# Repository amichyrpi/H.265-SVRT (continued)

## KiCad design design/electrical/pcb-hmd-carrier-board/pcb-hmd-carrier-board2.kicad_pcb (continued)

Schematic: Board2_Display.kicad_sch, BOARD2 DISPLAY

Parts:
C260, C265: 2.2uF; C_0603_1608Metric
C261, C262, C266, C267: 1uF 10V; C_0603_1608Metric
C270, C272, C273: 4.7uF 10V; C_0603_1608Metric
C271: 2.2uF 10V; C_0603_1608Metric
C274: 1uF; C_0603_1608Metric
C280: 68n COMP; C_0402_1005Metric
C281: 10uF 10V; C_0402_1005Metric
C282, C283: 10uF 16V; C_0402_1005Metric
C290, C291: 100n; C_0402_1005Metric
D201: DFLS160-7; D_SOD-123
J201: J_DISPLAY_LEFT 245863050104829+; Kyocera_245863050104829_50P_P0.35
J202: J_DISPLAY_RIGHT 245863050104829+; Kyocera_245863050104829_50P_P0.35
L203, L204, L205, L206: 2.2uH; L_Abracon_ASPI-4030S
L207: 4.7uH 1.6A DFE252010; L_APV_ANR252010
L208: 10uH >=2.5A WLED; L_Abracon_ASPI-4030S
R260, R265: 100k RESET pulldown; R_0402_1005Metric
R261, R266: 0R DNP to BL_PWM; R_0402_1005Metric; not fitted
R280: 37.4k 1% ISET=33.2mA; R_0402_1005Metric
R281: 49.9k 1% 1.25MHz; R_0402_1005Metric
R282: 147k 1% OVP; R_0402_1005Metric
R283: 20k 1% OVP; R_0402_1005Metric
R284: 3k COMP; R_0402_1005Metric
R290, R291, R292, R293: 2.2k I2C; R_0402_1005Metric
R294, R295: 10k; R_0402_1005Metric
TP201: DISPLAY_5V; TestPoint_Pad_D1.0mm
TP202: DISPLAY_3V3; TestPoint_Pad_D1.0mm
TP203: DISPLAY_1V8; TestPoint_Pad_D1.0mm
TP204: DISPLAY_1V2; TestPoint_Pad_D1.0mm
TP205: DISPLAY_1V15; TestPoint_Pad_D1.0mm
TP206: LCD_VSP +5V5; TestPoint_Pad_D1.0mm
TP207: LCD_VSN -5V5; TestPoint_Pad_D1.0mm
TP208: BL_EN; TestPoint_Pad_D1.0mm
TP209: BL_PWM GPIO12; TestPoint_Pad_D1.0mm
TP210: I2C_SDA_1V8; TestPoint_Pad_D1.0mm
TP211: I2C_SCL_1V8; TestPoint_Pad_D1.0mm
TP260: L S1_TEST NC; TestPoint_Pad_D1.0mm
TP261: L TE; TestPoint_Pad_D1.0mm
TP262: L LEDPWM; TestPoint_Pad_D1.0mm
TP265: R S1_TEST NC; TestPoint_Pad_D1.0mm
TP266: R TE; TestPoint_Pad_D1.0mm
TP267: R LEDPWM; TestPoint_Pad_D1.0mm
U201, U202: TC358870XBG(NOK) C3008712; Toshiba_P-VFBGA80_7x7mm_P0.65
U203, U204, U205, U206: TLV62569DBVR; SOT-23-5
U207: TPS65132B5YFFR; TI_DSBGA15_YFF_2.108x1.514mm_P0.4
U208: MP3387AGRT-P; TQFN-24-1EP_4x4mm_P0.5mm_EP2.6x2.6mm
U209: PCA9306DCTR C123752; TSSOP-8_3x3mm_P0.65mm
Y201, Y202: SIT8008ACE73-18E-48.000000E; Oscillator_SMD_SiT_PQFN-4Pin_2.0x1.6mm

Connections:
+3V3: R290.2 (+3V3), R291.2 (+3V3), U209.2 (+3V3); also elsewhere on the board
+5V_SYS: C270.1 (+5V_SYS), C281.1 (+5V_SYS), L207.1 (+5V_SYS), L208.1 (+5V_SYS), TP201.1, U203.1 (+5V_SYS), U203.4 (+5V_SYS), U204.1 (+5V_SYS), U204.4 (+5V_SYS), U205.1 (+5V_SYS), U205.4 (+5V_SYS), U206.1 (+5V_SYS), U206.4 (+5V_SYS), U207.C1 (+5V_SYS), U208.23 (+5V_SYS), U208.24 (+5V_SYS); also elsewhere on the board
BIAS_FLY1: C271.1 (BIAS_FLY1), U207.C3 (BIAS_FLY1)
BIAS_FLY2: C271.2 (BIAS_FLY2), U207.A3 (BIAS_FLY2)
BIAS_REG: C274.1 (BIAS_REG), U207.D3 (BIAS_REG), U207.E2 (BIAS_REG)
BIAS_SW: L207.2 (BIAS_SW), U207.D1 (BIAS_SW)
BL_EN: TP208.1, U208.1 (BL_EN); also elsewhere on the board
BL_PWM: R261.2 (BL_PWM), R266.2 (BL_PWM), TP209.1, U208.6 (BL_PWM); also elsewhere on the board
DISPLAY_1V2: L205.2 (DISPLAY_1V2), TP204.1; also elsewhere on the board
DISPLAY_1V8: C260.1 (DISPLAY_1V8), C265.1 (DISPLAY_1V8), C290.1 (DISPLAY_1V8), C291.1 (DISPLAY_1V8), J201.2 (DISPLAY_1V8), J201.4 (DISPLAY_1V8), J202.2 (DISPLAY_1V8), J202.4 (DISPLAY_1V8), L204.2 (DISPLAY_1V8), R292.2 (DISPLAY_1V8), R293.2 (DISPLAY_1V8), R294.2 (DISPLAY_1V8), R295.2 (DISPLAY_1V8), TP203.1, U209.3 (DISPLAY_1V8), U209.4 (DISPLAY_1V8), Y201.1 (DISPLAY_1V8), Y201.4 (DISPLAY_1V8), Y202.1 (DISPLAY_1V8), Y202.4 (DISPLAY_1V8); also elsewhere on the board
DISPLAY_1V15: L206.2 (DISPLAY_1V15), TP205.1; also elsewhere on the board
DISPLAY_3V3: L203.2 (DISPLAY_3V3), TP202.1; also elsewhere on the board
DISPLAY_GPIO_INT_N: R295.1 (DISPLAY_GPIO_INT_N); also elsewhere on the board
DISPLAY_GPIO_RESETN: R294.1 (DISPLAY_GPIO_RESETN); also elsewhere on the board
DISPLAY_I2C_SCL_1V8: R293.1 (DISPLAY_I2C_SCL_1V8), TP211.1, U201.K4 (DISPLAY_I2C_SCL_1V8), U202.K4 (DISPLAY_I2C_SCL_1V8), U207.B2 (DISPLAY_I2C_SCL_1V8), U209.5 (DISPLAY_I2C_SCL_1V8); also elsewhere on the board
DISPLAY_I2C_SDA_1V8: R292.1 (DISPLAY_I2C_SDA_1V8), TP210.1, U201.K3 (DISPLAY_I2C_SDA_1V8), U202.K3 (DISPLAY_I2C_SDA_1V8), U207.C2 (DISPLAY_I2C_SDA_1V8), U209.6 (DISPLAY_I2C_SDA_1V8); also elsewhere on the board
GND: C260.2 (GND), C261.2 (GND), C262.2 (GND), C265.2 (GND), C266.2 (GND), C267.2 (GND), C270.2 (GND), C272.2 (GND), C273.2 (GND), C274.2 (GND), C280.2 (GND), C281.2 (GND), C282.2 (GND), C283.2 (GND), C290.2 (GND), C291.2 (GND), J201.1 (GND), J201.5 (GND), J201.6 (GND), J201.9 (GND), J201.10 (GND), J201.15 (GND), J201.16 (GND), J201.21 (GND), J201.22 (GND), J201.27 (GND), J201.28 (GND), J201.33 (GND), J201.34 (GND), J201.39 (GND), J201.40 (GND), J201.43 (GND), J201.46 (GND), J201.50 (GND), J202.1 (GND), J202.5 (GND), J202.6 (GND), J202.9 (GND), J202.10 (GND), J202.15 (GND), J202.16 (GND), J202.21 (GND), J202.22 (GND), J202.27 (GND), J202.28 (GND), J202.33 (GND), J202.34 (GND), J202.39 (GND), J202.40 (GND), J202.43 (GND), J202.46 (GND), J202.50 (GND), R260.2 (GND), R265.2 (GND), R280.2 (GND), R281.2 (GND), R283.2 (GND), U201.A10 (GND), U201.C9 (GND), U201.D4 (GND), U201.D5 (GND), U201.D6 (GND), U201.D7 (GND), U201.E4 (GND), U201.E5 (GND), U201.E6 (GND), U201.E7 (GND), U201.F4 (GND), U201.F5 (GND), U201.F6 (GND), U201.F7 (GND), U201.G4 (GND), U201.G5 (GND), U201.G6 (GND), U201.G7 (GND), U201.H1 (GND), U201.K10 (GND), U202.A10 (GND), U202.C9 (GND), U202.D4 (GND), U202.D5 (GND), U202.D6 (GND), U202.D7 (GND), U202.E4 (GND), U202.E5 (GND), U202.E6 (GND), U202.E7 (GND), U202.F4 (GND), U202.F5 (GND), U202.F6 (GND), U202.F7 (GND), U202.G4 (GND), U202.G5 (GND), U202.G6 (GND), U202.G7 (GND), U202.H1 (GND), U202.K10 (GND), U203.2 (GND), U204.2 (GND), U205.2 (GND), U206.2 (GND), U207.B3 (GND), U207.D2 (GND), U207.E1 (GND), U208.3 (GND), U208.4 (GND), U208.5 (GND), U208.7 (GND), U208.8 (GND), U208.17 (GND), U208.18 (GND), U208.21 (GND), U208.25 (GND), U209.1 (GND), Y201.2 (GND), Y202.2 (GND); also elsewhere on the board
HDMI_L_CEC: U201.A2 (HDMI_L_CEC); also elsewhere on the board
HDMI_L_CLK_N: U201.C2 (HDMI_L_CLK_N); also elsewhere on the board
HDMI_L_CLK_P: U201.C1 (HDMI_L_CLK_P); also elsewhere on the board
HDMI_L_D0_N: U201.D2 (HDMI_L_D0_N); also elsewhere on the board
HDMI_L_D0_P: U201.D1 (HDMI_L_D0_P); also elsewhere on the board
HDMI_L_D1_N: U201.E2 (HDMI_L_D1_N); also elsewhere on the board
HDMI_L_D1_P: U201.E1 (HDMI_L_D1_P); also elsewhere on the board
HDMI_L_D2_N: U201.F2 (HDMI_L_D2_N); also elsewhere on the board
HDMI_L_D2_P: U201.F1 (HDMI_L_D2_P); also elsewhere on the board
HDMI_L_DDC_SCL: U201.A3 (HDMI_L_DDC_SCL); also elsewhere on the board
HDMI_L_DDC_SDA: U201.B3 (HDMI_L_DDC_SDA); also elsewhere on the board
HDMI_L_HPD: U201.B4 (HDMI_L_HPD); also elsewhere on the board
HDMI_R_CEC: U202.A2 (HDMI_R_CEC); also elsewhere on the board
HDMI_R_CLK_N: U202.C2 (HDMI_R_CLK_N); also elsewhere on the board
HDMI_R_CLK_P: U202.C1 (HDMI_R_CLK_P); also elsewhere on the board
HDMI_R_D0_N: U202.D2 (HDMI_R_D0_N); also elsewhere on the board
HDMI_R_D0_P: U202.D1 (HDMI_R_D0_P); also elsewhere on the board
HDMI_R_D1_N: U202.E2 (HDMI_R_D1_N); also elsewhere on the board
HDMI_R_D1_P: U202.E1 (HDMI_R_D1_P); also elsewhere on the board
HDMI_R_D2_N: U202.F2 (HDMI_R_D2_N); also elsewhere on the board
HDMI_R_D2_P: U202.F1 (HDMI_R_D2_P); also elsewhere on the board
HDMI_R_DDC_SCL: U202.A3 (HDMI_R_DDC_SCL); also elsewhere on the board
HDMI_R_DDC_SDA: U202.B3 (HDMI_R_DDC_SDA); also elsewhere on the board
HDMI_R_HPD: U202.B4 (HDMI_R_HPD); also elsewhere on the board
I2C_SCL: R291.1 (I2C_SCL), U209.8 (I2C_SCL); also elsewhere on the board
I2C_SDA: R290.1 (I2C_SDA), U209.7 (I2C_SDA); also elsewhere on the board
LCD_BIAS_ENN: U207.A1 (LCD_BIAS_ENN); also elsewhere on the board
LCD_BIAS_ENP: U207.B1 (LCD_BIAS_ENP); also elsewhere on the board
LCD_VSN: C262.1 (LCD_VSN), C267.1 (LCD_VSN), C273.1 (LCD_VSN), J201.7 (LCD_VSN), J202.7 (LCD_VSN), TP207.1, U207.A2 (LCD_VSN)
LCD_VSP: C261.1 (LCD_VSP), C266.1 (LCD_VSP), C272.1 (LCD_VSP), J201.3 (LCD_VSP), J202.3 (LCD_VSP), TP206.1, U207.E3 (LCD_VSP)
LED_BOOST: C282.1 (LED_BOOST), C283.1 (LED_BOOST), D201.1 (LED_BOOST), J201.41 (LED_BOOST), J202.41 (LED_BOOST), R282.1 (LED_BOOST)
L_1V2_MIPI0: U201.J10 (L_1V2_MIPI0); also elsewhere on the board
L_1V2_MIPI1: U201.B10 (L_1V2_MIPI1); also elsewhere on the board
L_1V8_IO: U201.J7 (L_1V8_IO); also elsewhere on the board
L_1V15_CORE: U201.C10 (L_1V15_CORE), U201.K6 (L_1V15_CORE); also elsewhere on the board
L_1V15_HDMI: U201.B2 (L_1V15_HDMI), U201.G2 (L_1V15_HDMI); also elsewhere on the board
L_3V3_HDMI: U201.B1 (L_3V3_HDMI), U201.G1 (L_3V3_HDMI); also elsewhere on the board
L_3V3_IO: U201.H2 (L_3V3_IO); also elsewhere on the board
L_BIASDA: U201.J1 (L_BIASDA); also elsewhere on the board
L_BRIDGE_INT: U201.J3 (L_BRIDGE_INT); also elsewhere on the board
L_BRIDGE_RESETN: U201.K8 (L_BRIDGE_RESETN); also elsewhere on the board
L_DSIA_CLK_N: J201.18 (L_DSIA_CLK_N), U201.F9 (L_DSIA_CLK_N)
L_DSIA_CLK_P: J201.20 (L_DSIA_CLK_P), U201.F10 (L_DSIA_CLK_P)
L_DSIA_D0_N: J201.11 (L_DSIA_D0_N), U201.H9 (L_DSIA_D0_N)
L_DSIA_D0_P: J201.13 (L_DSIA_D0_P), U201.H10 (L_DSIA_D0_P)
L_DSIA_D1_N: J201.17 (L_DSIA_D1_N), U201.G9 (L_DSIA_D1_N)
L_DSIA_D1_P: J201.19 (L_DSIA_D1_P), U201.G10 (L_DSIA_D1_P)
L_DSIA_D2_N: J201.24 (L_DSIA_D2_N), U201.E9 (L_DSIA_D2_N)
L_DSIA_D2_P: J201.26 (L_DSIA_D2_P), U201.E10 (L_DSIA_D2_P)
L_DSIA_D3_N: J201.12 (L_DSIA_D3_N), U201.D9 (L_DSIA_D3_N)
L_DSIA_D3_P: J201.14 (L_DSIA_D3_P), U201.D10 (L_DSIA_D3_P)
L_DSIB_CLK_N: J201.31 (L_DSIB_CLK_N), U201.B7 (L_DSIB_CLK_N)
L_DSIB_CLK_P: J201.29 (L_DSIB_CLK_P), U201.A7 (L_DSIB_CLK_P)
L_DSIB_D0_N: J201.38 (L_DSIB_D0_N), U201.B9 (L_DSIB_D0_N)
L_DSIB_D0_P: J201.36 (L_DSIB_D0_P), U201.A9 (L_DSIB_D0_P)
L_DSIB_D1_N: J201.32 (L_DSIB_D1_N), U201.B8 (L_DSIB_D1_N)
L_DSIB_D1_P: J201.30 (L_DSIB_D1_P), U201.A8 (L_DSIB_D1_P)
L_DSIB_D2_N: J201.25 (L_DSIB_D2_N), U201.B6 (L_DSIB_D2_N)
L_DSIB_D2_P: J201.23 (L_DSIB_D2_P), U201.A6 (L_DSIB_D2_P)
L_DSIB_D3_N: J201.37 (L_DSIB_D3_N), U201.B5 (L_DSIB_D3_N)
L_DSIB_D3_P: J201.35 (L_DSIB_D3_P), U201.A5 (L_DSIB_D3_P)
L_HPDI: U201.A4 (L_HPDI); also elsewhere on the board
L_LCD_LEDPWM: J201.48 (L_LCD_LEDPWM), R261.1 (L_LCD_LEDPWM), TP262.1; also elsewhere on the board
L_LCD_RESET: J201.42 (L_LCD_RESET), R260.1 (L_LCD_RESET); also elsewhere on the board
L_LCD_TE: J201.44 (L_LCD_TE), TP261.1; also elsewhere on the board
L_LED1_N: J201.45 (L_LED1_N), U208.15 (L_LED1_N)
L_LED2_N: J201.47 (L_LED2_N), U208.14 (L_LED2_N)
L_LED3_N: J201.49 (L_LED3_N), U208.13 (L_LED3_N)
L_PCKIN: U201.K1 (L_PCKIN); also elsewhere on the board
L_PFIL: U201.K2 (L_PFIL); also elsewhere on the board
L_REFCLK: U201.K9 (L_REFCLK), Y201.3 (L_REFCLK)
L_REXT: U201.A1 (L_REXT); also elsewhere on the board
L_S1_TEST: J201.8 (L_S1_TEST), TP260.1
REG_1V2_FB: U205.5 (REG_1V2_FB); also elsewhere on the board
REG_1V2_SW: L205.1 (REG_1V2_SW), U205.3 (REG_1V2_SW)
REG_1V8_FB: U204.5 (REG_1V8_FB); also elsewhere on the board
REG_1V8_SW: L204.1 (REG_1V8_SW), U204.3 (REG_1V8_SW)
REG_1V15_FB: U206.5 (REG_1V15_FB); also elsewhere on the board
REG_1V15_SW: L206.1 (REG_1V15_SW), U206.3 (REG_1V15_SW)
REG_3V3_FB: U203.5 (REG_3V3_FB); also elsewhere on the board
REG_3V3_SW: L203.1 (REG_3V3_SW), U203.3 (REG_3V3_SW)
R_1V2_MIPI0: U202.J10 (R_1V2_MIPI0); also elsewhere on the board
R_1V2_MIPI1: U202.B10 (R_1V2_MIPI1); also elsewhere on the board
R_1V8_IO: U202.J7 (R_1V8_IO); also elsewhere on the board
R_1V15_CORE: U202.C10 (R_1V15_CORE), U202.K6 (R_1V15_CORE); also elsewhere on the board
R_1V15_HDMI: U202.B2 (R_1V15_HDMI), U202.G2 (R_1V15_HDMI); also elsewhere on the board
R_3V3_HDMI: U202.B1 (R_3V3_HDMI), U202.G1 (R_3V3_HDMI); also elsewhere on the board
R_3V3_IO: U202.H2 (R_3V3_IO); also elsewhere on the board
R_BIASDA: U202.J1 (R_BIASDA); also elsewhere on the board
R_BRIDGE_INT: U202.J3 (R_BRIDGE_INT); also elsewhere on the board
R_BRIDGE_RESETN: U202.K8 (R_BRIDGE_RESETN); also elsewhere on the board
R_DSIA_CLK_N: J202.18 (R_DSIA_CLK_N), U202.F9 (R_DSIA_CLK_N)
R_DSIA_CLK_P: J202.20 (R_DSIA_CLK_P), U202.F10 (R_DSIA_CLK_P)
R_DSIA_D0_N: J202.11 (R_DSIA_D0_N), U202.H9 (R_DSIA_D0_N)
R_DSIA_D0_P: J202.13 (R_DSIA_D0_P), U202.H10 (R_DSIA_D0_P)
R_DSIA_D1_N: J202.17 (R_DSIA_D1_N), U202.G9 (R_DSIA_D1_N)
R_DSIA_D1_P: J202.19 (R_DSIA_D1_P), U202.G10 (R_DSIA_D1_P)
R_DSIA_D2_N: J202.24 (R_DSIA_D2_N), U202.E9 (R_DSIA_D2_N)
R_DSIA_D2_P: J202.26 (R_DSIA_D2_P), U202.E10 (R_DSIA_D2_P)
R_DSIA_D3_N: J202.12 (R_DSIA_D3_N), U202.D9 (R_DSIA_D3_N)
R_DSIA_D3_P: J202.14 (R_DSIA_D3_P), U202.D10 (R_DSIA_D3_P)
R_DSIB_CLK_N: J202.31 (R_DSIB_CLK_N), U202.B7 (R_DSIB_CLK_N)
R_DSIB_CLK_P: J202.29 (R_DSIB_CLK_P), U202.A7 (R_DSIB_CLK_P)
R_DSIB_D0_N: J202.38 (R_DSIB_D0_N), U202.B9 (R_DSIB_D0_N)
R_DSIB_D0_P: J202.36 (R_DSIB_D0_P), U202.A9 (R_DSIB_D0_P)
R_DSIB_D1_N: J202.32 (R_DSIB_D1_N), U202.B8 (R_DSIB_D1_N)
R_DSIB_D1_P: J202.30 (R_DSIB_D1_P), U202.A8 (R_DSIB_D1_P)
R_DSIB_D2_N: J202.25 (R_DSIB_D2_N), U202.B6 (R_DSIB_D2_N)
R_DSIB_D2_P: J202.23 (R_DSIB_D2_P), U202.A6 (R_DSIB_D2_P)
R_DSIB_D3_N: J202.37 (R_DSIB_D3_N), U202.B5 (R_DSIB_D3_N)
R_DSIB_D3_P: J202.35 (R_DSIB_D3_P), U202.A5 (R_DSIB_D3_P)
R_HPDI: U202.A4 (R_HPDI); also elsewhere on the board
R_LCD_LEDPWM: J202.48 (R_LCD_LEDPWM), R266.1 (R_LCD_LEDPWM), TP267.1; also elsewhere on the board
R_LCD_RESET: J202.42 (R_LCD_RESET), R265.1 (R_LCD_RESET); also elsewhere on the board
R_LCD_TE: J202.44 (R_LCD_TE), TP266.1; also elsewhere on the board
R_LED1_N: J202.45 (R_LED1_N), U208.12 (R_LED1_N)
R_LED2_N: J202.47 (R_LED2_N), U208.10 (R_LED2_N)
R_LED3_N: J202.49 (R_LED3_N), U208.9 (R_LED3_N)
R_PCKIN: U202.K1 (R_PCKIN); also elsewhere on the board
R_PFIL: U202.K2 (R_PFIL); also elsewhere on the board
R_REFCLK: U202.K9 (R_REFCLK), Y202.3 (R_REFCLK)
R_REXT: U202.A1 (R_REXT); also elsewhere on the board
R_S1_TEST: J202.8 (R_S1_TEST), TP265.1
WLED_COMP: R284.1 (WLED_COMP), U208.22 (WLED_COMP)
WLED_COMP_RC: C280.1 (WLED_COMP_RC), R284.2 (WLED_COMP_RC)
WLED_FREQ: R281.1 (WLED_FREQ), U208.2 (WLED_FREQ)
WLED_ISET: R280.1 (WLED_ISET), U208.11 (WLED_ISET)
WLED_OVP: R282.2 (WLED_OVP), R283.1 (WLED_OVP), U208.16 (WLED_OVP)
WLED_SW: D201.2 (WLED_SW), L208.2 (WLED_SW), U208.19 (WLED_SW), U208.20 (WLED_SW)

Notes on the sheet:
BOARD2 DISPLAY
Recovered from approved PCB placement; passive pin types marked VERIFY until vendor-symbol audit

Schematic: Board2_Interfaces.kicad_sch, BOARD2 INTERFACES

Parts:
D1: TVS2200DRVR; WSON-6-1EP_2x2mm_P0.65mm_EP1x1.6mm
D11: TJ-S3227 RGB COMMON ANODE C601674; TOGIALED_TJ-S3227SW1TCGLCCYRGB-A5
J2: BM28 BATTERY FLEX 5A + NTC/ID; Hirose_BM28B0.6-20DS_2-0.35V
J6: TAG-CONNECT SERVICE PADS (NO FIT); Tag-Connect_TC2050-IDC-NL_2x05_P1.27mm_Vertical
J7: DF40C-100DP-0.4V(51) TRACKING; Hirose_DF40C-100DP-0.4V_2x50-1MP_P0.4mm
J9: DX07S016JA1R1500 CHARGE/SERVICE; USB_C_Receptacle_JAE_DX07S016JA1R1500
J10: PROX SENSOR - SM05B-SURS-TF; JST_SUR_SM05B-SURS-TF_1x05-1MP_P0.80mm_Horizontal
J11: BM28B0.6-20DS/2-0.35V BUTTON FLEX; Hirose_BM28B0.6-20DS_2-0.35V_BUTTONS
R73, R76, R77, R78: 1k; R_0402_1005Metric
R74, R75: 330R; R_0402_1005Metric
TP1, TP9, TP10, TP11, TP12, TP13, TP14, TP15, TP16, TP17, TP18, TP19, TP20, TP21, TP22, TP23: CHG_STAT; TestPoint_Pad_D1.0mm
TP2: PGOOD_5V; TestPoint_Pad_D1.0mm
TP3: BAT_ID; TestPoint_Pad_D1.0mm
TP4: +5V_SYS; TestPoint_Pad_D1.0mm
TP5: +3V3; TestPoint_Pad_D1.0mm
TP6: +1V05_USB; TestPoint_Pad_D1.0mm
TP7: GND; TestPoint_Pad_D1.0mm
TP8: VBAT_SYS; TestPoint_Pad_D1.0mm
U210: TCA9539PWR 1V8 DISPLAY GPIO; TSSOP-24_4.4x7.8mm_P0.65mm

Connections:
+1V05_USB: TP6.1; also elsewhere on the board
+3V3: D11.1 (+3V3), J6.1 (+3V3), J10.4 (+3V3), TP5.1; also elsewhere on the board
+5V_SYS: TP4.1; also elsewhere on the board
BAT_ID: TP3.1
BL_EN: U210.13 (BL_EN); also elsewhere on the board
CC1: J9.A5 (CC1); also elsewhere on the board
CC2: J9.B5 (CC2); also elsewhere on the board
CHG_STAT: TP1.1; also elsewhere on the board
CM4_EXT_RESET_N: J6.8 (CM4_EXT_RESET_N); also elsewhere on the board
DISPLAY_1V8: U210.24 (DISPLAY_1V8); also elsewhere on the board
DISPLAY_GPIO_INT_N: U210.1 (DISPLAY_GPIO_INT_N); also elsewhere on the board
DISPLAY_GPIO_RESETN: U210.3 (DISPLAY_GPIO_RESETN); also elsewhere on the board
DISPLAY_I2C_SCL_1V8: U210.22 (DISPLAY_I2C_SCL_1V8); also elsewhere on the board
DISPLAY_I2C_SDA_1V8: U210.23 (DISPLAY_I2C_SDA_1V8); also elsewhere on the board
EMMC_BOOT_N: J6.7 (EMMC_BOOT_N); also elsewhere on the board
GND: D1.1 (GND), D1.2 (GND), D1.3 (GND), D1.7 (GND), J6.2 (GND), J6.10 (GND), J9.A1 (GND), J9.A12 (GND), J9.B1 (GND), J9.B12 (GND), J10.5 (GND), J11.21 (GND), TP7.1, U210.2 (GND), U210.12 (GND), U210.21 (GND); also elsewhere on the board
I2C_SCL: J6.4 (I2C_SCL), J10.3 (I2C_SCL); also elsewhere on the board
I2C_SDA: J6.3 (I2C_SDA), J10.2 (I2C_SDA); also elsewhere on the board
LCD_BIAS_ENN: U210.19 (LCD_BIAS_ENN); also elsewhere on the board
LCD_BIAS_ENP: U210.18 (LCD_BIAS_ENP); also elsewhere on the board
LED_BLUE_GPIO16_N: R75.1 (LED_BLUE_GPIO16_N); also elsewhere on the board
LED_BLUE_K: D11.4 (LED_BLUE_K), R75.2 (LED_BLUE_K)
LED_GREEN_GPIO13_N: R74.1 (LED_GREEN_GPIO13_N); also elsewhere on the board
LED_GREEN_K: D11.3 (LED_GREEN_K), R74.2 (LED_GREEN_K)
LED_RED_K: D11.2 (LED_RED_K), R73.2 (LED_RED_K)
L_BRIDGE_INT: U210.6 (L_BRIDGE_INT); also elsewhere on the board
L_BRIDGE_RESETN: U210.4 (L_BRIDGE_RESETN); also elsewhere on the board
L_HPDI: U210.16 (L_HPDI); also elsewhere on the board
L_LCD_LEDPWM: U210.14 (L_LCD_LEDPWM); also elsewhere on the board
L_LCD_RESET: U210.8 (L_LCD_RESET); also elsewhere on the board
L_LCD_TE: U210.10 (L_LCD_TE); also elsewhere on the board
PGOOD_5V: TP2.1; also elsewhere on the board
PROX_INT: J10.1 (PROX_INT); also elsewhere on the board
PWR_KEY_GPIO26_N: R76.1 (PWR_KEY_GPIO26_N); also elsewhere on the board
PWR_KEY_N: J11.1 (PWR_KEY_N), R76.2 (PWR_KEY_N)
RUN_PG: J6.9 (RUN_PG); also elsewhere on the board
R_BRIDGE_INT: U210.7 (R_BRIDGE_INT); also elsewhere on the board
R_BRIDGE_RESETN: U210.5 (R_BRIDGE_RESETN); also elsewhere on the board
R_HPDI: U210.17 (R_HPDI); also elsewhere on the board
R_LCD_LEDPWM: U210.15 (R_LCD_LEDPWM); also elsewhere on the board
R_LCD_RESET: U210.9 (R_LCD_RESET); also elsewhere on the board
R_LCD_TE: U210.11 (R_LCD_TE); also elsewhere on the board
UART_RX: J6.6 (UART_RX); also elsewhere on the board
UART_TX: J6.5 (UART_TX); also elsewhere on the board
USB2_SERVICE_DM: J9.A7 (USB2_SERVICE_DM), J9.B7 (USB2_SERVICE_DM); also elsewhere on the board
USB2_SERVICE_DP: J9.A6 (USB2_SERVICE_DP), J9.B6 (USB2_SERVICE_DP); also elsewhere on the board
VBAT_SYS: TP8.1; also elsewhere on the board
VBUS_CHARGE: D1.4 (VBUS_CHARGE), D1.5 (VBUS_CHARGE), D1.6 (VBUS_CHARGE), J9.A4 (VBUS_CHARGE), J9.A9 (VBUS_CHARGE), J9.B4 (VBUS_CHARGE), J9.B9 (VBUS_CHARGE); also elsewhere on the board
VOL_DOWN_GPIO17_N: R78.1 (VOL_DOWN_GPIO17_N); also elsewhere on the board
VOL_DOWN_N: J11.17 (VOL_DOWN_N), R78.2 (VOL_DOWN_N)
VOL_UP_GPIO24_N: R77.1 (VOL_UP_GPIO24_N); also elsewhere on the board
VOL_UP_N: J11.9 (VOL_UP_N), R77.2 (VOL_UP_N)
nPI_LED_PWR: R73.1 (nPI_LED_PWR); also elsewhere on the board

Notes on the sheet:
BOARD2 INTERFACES
Recovered from approved PCB placement; passive pin types marked VERIFY until vendor-symbol audit

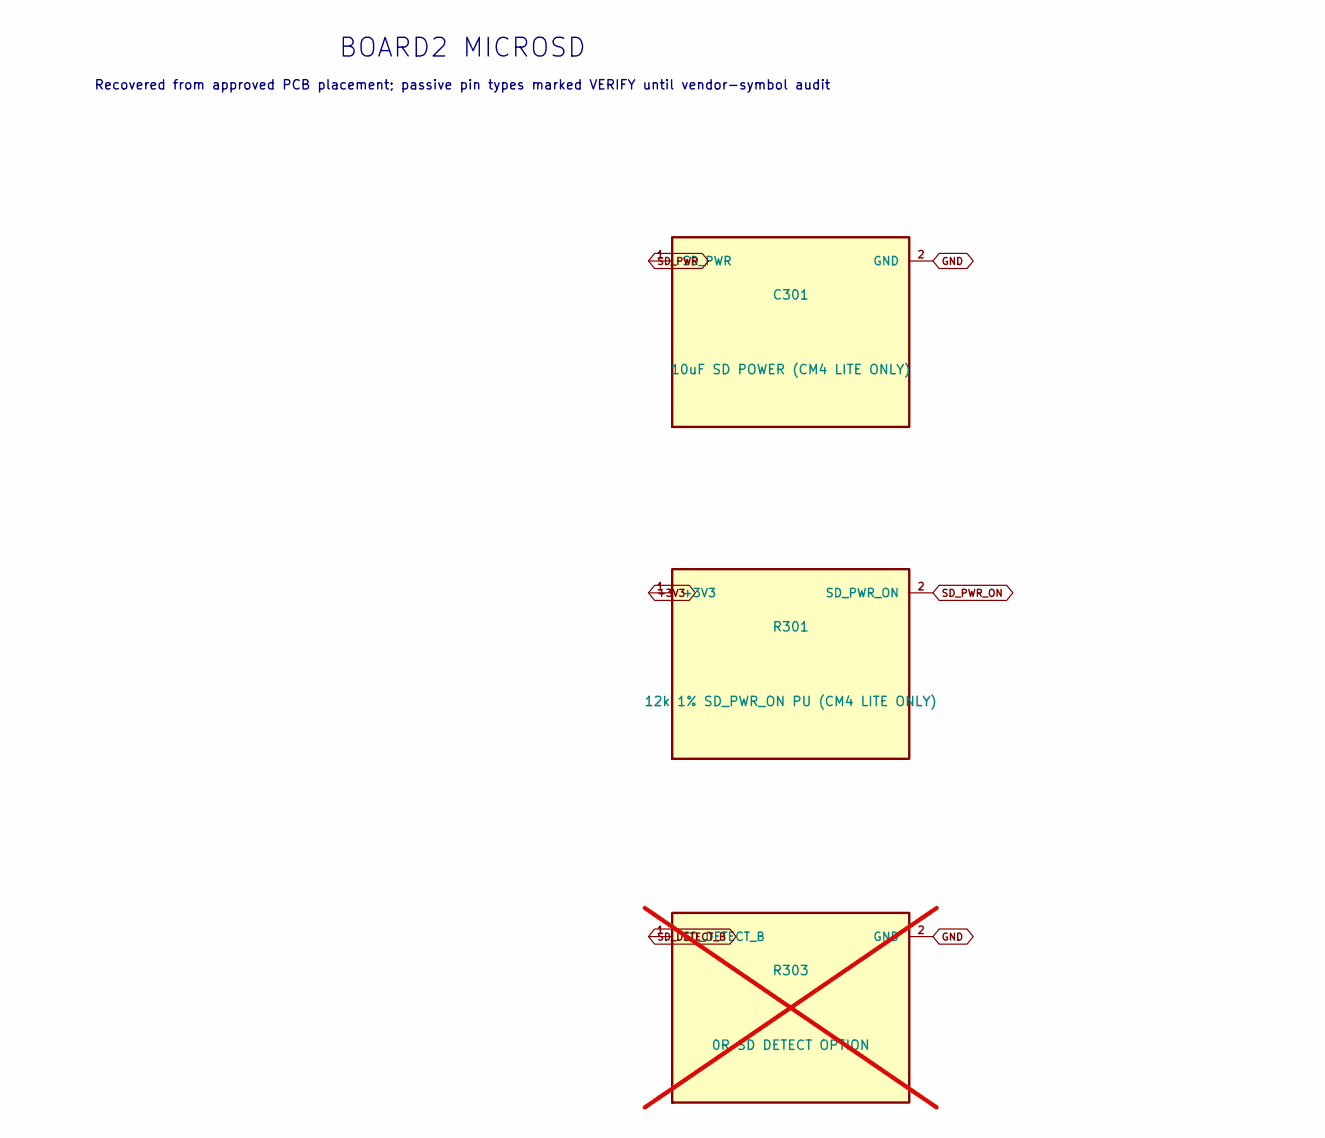
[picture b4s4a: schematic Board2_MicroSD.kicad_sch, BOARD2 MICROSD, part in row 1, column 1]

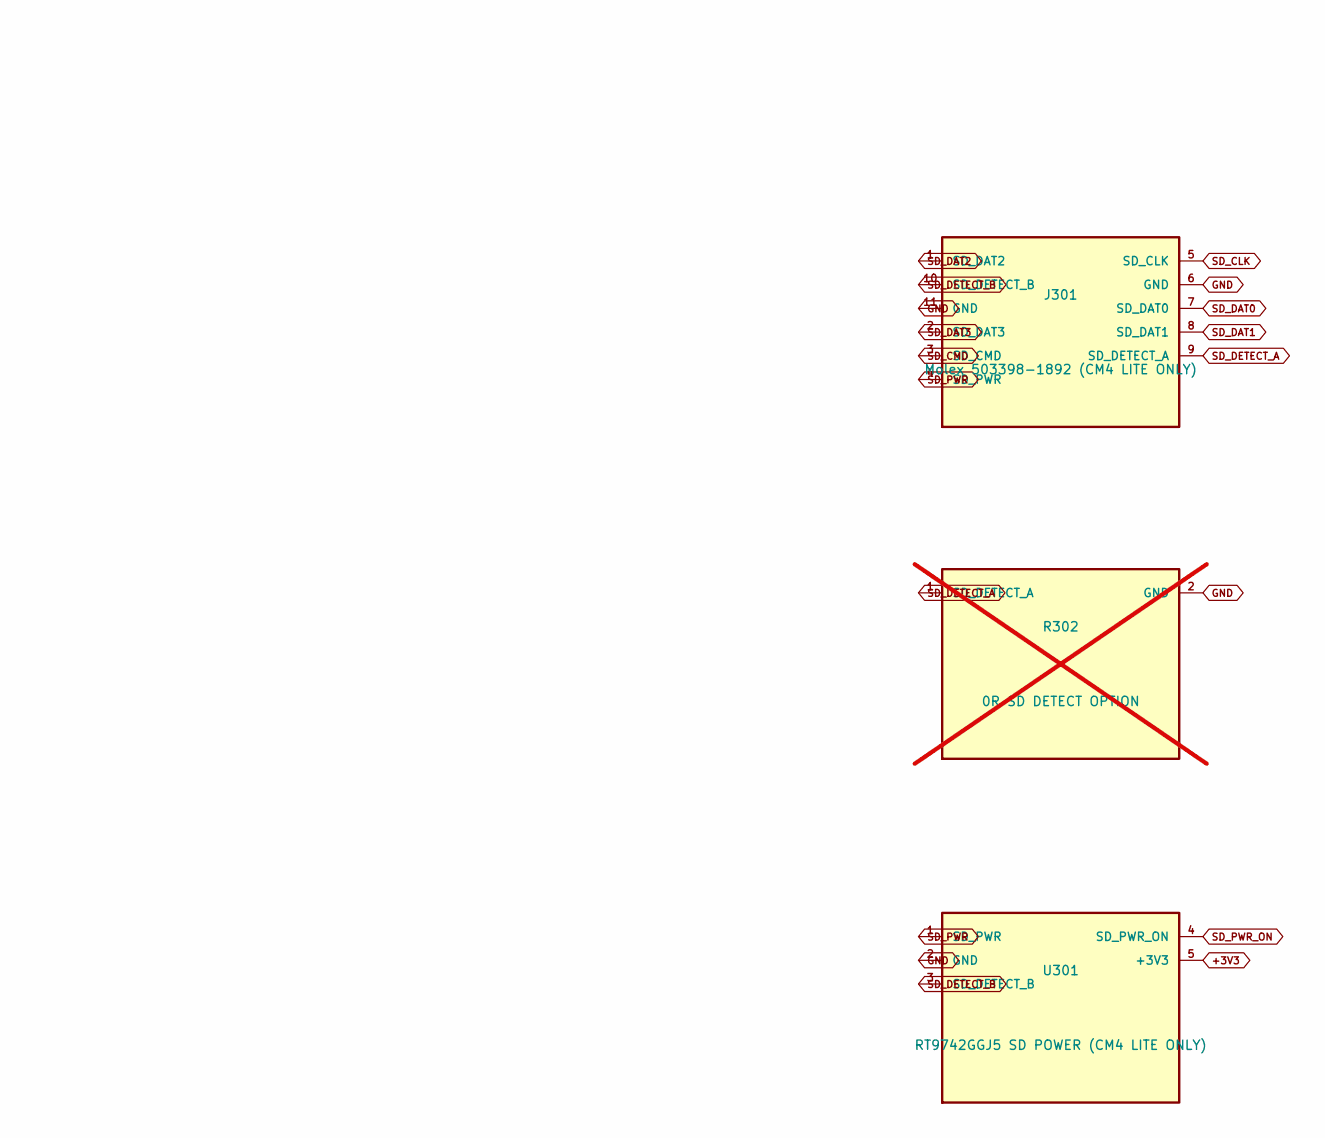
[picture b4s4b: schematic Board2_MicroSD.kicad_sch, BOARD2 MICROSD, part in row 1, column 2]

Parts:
C301: 10uF SD POWER (CM4 LITE ONLY); C_0603_1608Metric
J301: Molex 503398-1892 (CM4 LITE ONLY); SDCARD_MOLEX_503398-1892
R301: 12k 1% SD_PWR_ON PU (CM4 LITE ONLY); R_0402_1005Metric
R302, R303: 0R SD DETECT OPTION; R_0402_1005Metric; not fitted
U301: RT9742GGJ5 SD POWER (CM4 LITE ONLY); SOT-23-5

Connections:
+3V3: R301.1 (+3V3), U301.5 (+3V3); also elsewhere on the board
GND: C301.2 (GND), J301.6 (GND), J301.11 (GND), R302.2 (GND), R303.2 (GND), U301.2 (GND); also elsewhere on the board
SD_CLK: J301.5 (SD_CLK); also elsewhere on the board
SD_CMD: J301.3 (SD_CMD); also elsewhere on the board
SD_DAT0: J301.7 (SD_DAT0); also elsewhere on the board
SD_DAT1: J301.8 (SD_DAT1); also elsewhere on the board
SD_DAT2: J301.1 (SD_DAT2); also elsewhere on the board
SD_DAT3: J301.2 (SD_DAT3); also elsewhere on the board
SD_DETECT_A: J301.9 (SD_DETECT_A), R302.1 (SD_DETECT_A)
SD_DETECT_B: J301.10 (SD_DETECT_B), R303.1 (SD_DETECT_B), U301.3 (SD_DETECT_B)
SD_PWR: C301.1 (SD_PWR), J301.4 (SD_PWR), U301.1 (SD_PWR)
SD_PWR_ON: R301.2 (SD_PWR_ON), U301.4 (SD_PWR_ON); also elsewhere on the board

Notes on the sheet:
BOARD2 MICROSD
Recovered from approved PCB placement; passive pin types marked VERIFY until vendor-symbol audit

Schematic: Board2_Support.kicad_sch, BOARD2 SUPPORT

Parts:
C1, C2, C3, C13, C14: 10u; C_0603_1608Metric
C7, C8: 330p; C_0603_1608Metric
C15: 100n; C_0603_1608Metric
C17, C18: 47n; C_0603_1608Metric
C27: 47p; C_0603_1608Metric
C64: 4.7u 10V; C_0603_1608Metric
C65, C66: 10u 6.3V; C_0603_1608Metric
C67: 120p C0G; C_0402_1005Metric
C2010, C2011, C2012, C2013, C2014, C2015, C2016, C2017, C2020, C2021, C2022, C2023, C2024, C2025, C2026, C2027, C20130, C20131, C20132, C20230, C20231, C20232: 100n; C_0402_1005Metric
C2032, C2042, C2052, C2062: 10uF 6.3V; C_0603_1608Metric
C20120, C20121, C20220, C20221: 1u; C_0603_1608Metric
C20122, C20123, C20222, C20223: 2.2u; C_0603_1608Metric
FB2011, FB2012, FB2013, FB2014, FB2015, FB2016, FB2017, FB2021, FB2022, FB2023, FB2024, FB2025, FB2026, FB2027: 600R@100MHz; L_0603_1608Metric
H1, H2, H3, H4, H5, H6: MountingHole_2.2mm_M2_DIN965_Pad_TopBottom
L1: 0.47uH XFL4015-471MEC; L_0402_1005Metric
L3: SRP5030CA-1R0M 1uH 9A; Bourns_SRP5030CA
R2: 30k; R_0402_1005Metric
R4: 137k ILIM; R_0402_1005Metric
R5, R6: 2.2k I2C; R_0402_1005Metric
R7, R2011, R2021: 10k; R_0402_1005Metric
R9: 30.1k TS; R_0402_1005Metric
R10: 10k NTC; R_0402_1005Metric
R12: 6.04k 2S; R_0402_1005Metric
R19: 75k 1V05 FB; R_0402_1005Metric
R20: 100k 1V05 FB; R_0402_1005Metric
R21: 100k 1V05 PG; R_0402_1005Metric
R22: 10k WIFI EN; R_0402_1005Metric
R23: 10k BT EN; R_0402_1005Metric
R25: 51k MODE; R_0402_1005Metric
R2010, R2020: 2.00k 1%; R_0402_1005Metric
R2012: 10k ADDR 0x0F; R_0402_1005Metric
R2022: 10k ADDR 0x1F; R_0402_1005Metric
R2031: 453k 1%; R_0402_1005Metric
R2032, R2042, R2051, R2052, R2062: 100k 1%; R_0402_1005Metric
R2041: 200k 1%; R_0402_1005Metric
R2061: 91k 1%; R_0402_1005Metric
U1: TPS62825DMQR; Texas_DMQ0006A_VSON-HR-6_1.5x1.5mm
U13: CAT24C512WI-GT3; TSSOP-8_3x3mm_P0.65mm

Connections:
+1V05_USB: C65.1 (+1V05_USB), C66.1 (+1V05_USB), C67.1 (+1V05_USB), L1.2 (+1V05_USB), R19.1 (+1V05_USB); also elsewhere on the board
+3V3: C3.1 (+3V3), C64.1 (+3V3), R21.1 (+3V3), R22.1 (+3V3), R23.1 (+3V3), U1.1 (+3V3), U1.6 (+3V3); also elsewhere on the board
BST1: C17.1 (BST1); also elsewhere on the board
BST2: C18.1 (BST2); also elsewhere on the board
BT_ENABLE_N: R23.2 (BT_ENABLE_N); also elsewhere on the board
CC1: C7.1 (CC1); also elsewhere on the board
CC2: C8.1 (CC2); also elsewhere on the board
DISPLAY_1V2: C2052.1 (DISPLAY_1V2), FB2016.1 (DISPLAY_1V2), FB2017.1 (DISPLAY_1V2), FB2026.1 (DISPLAY_1V2), FB2027.1 (DISPLAY_1V2), R2051.1 (DISPLAY_1V2); also elsewhere on the board
DISPLAY_1V8: C2010.1 (DISPLAY_1V8), C2020.1 (DISPLAY_1V8), C2042.1 (DISPLAY_1V8), FB2013.1 (DISPLAY_1V8), FB2023.1 (DISPLAY_1V8), R2022.2 (DISPLAY_1V8), R2041.1 (DISPLAY_1V8); also elsewhere on the board
DISPLAY_1V15: C2062.1 (DISPLAY_1V15), FB2014.1 (DISPLAY_1V15), FB2015.1 (DISPLAY_1V15), FB2024.1 (DISPLAY_1V15), FB2025.1 (DISPLAY_1V15), R2061.1 (DISPLAY_1V15); also elsewhere on the board
DISPLAY_3V3: C2032.1 (DISPLAY_3V3), FB2011.1 (DISPLAY_3V3), FB2012.1 (DISPLAY_3V3), FB2021.1 (DISPLAY_3V3), FB2022.1 (DISPLAY_3V3), R2031.1 (DISPLAY_3V3); also elsewhere on the board
FB_5V: C27.1 (FB_5V), R2.1 (FB_5V); also elsewhere on the board
GND: C1.2 (GND), C2.2 (GND), C3.2 (GND), C7.2 (GND), C8.2 (GND), C13.2 (GND), C14.2 (GND), C15.2 (GND), C27.2 (GND), C64.2 (GND), C65.2 (GND), C66.2 (GND), C2010.2 (GND), C2011.2 (GND), C2012.2 (GND), C2013.2 (GND), C2014.2 (GND), C2015.2 (GND), C2016.2 (GND), C2017.2 (GND), C2020.2 (GND), C2021.2 (GND), C2022.2 (GND), C2023.2 (GND), C2024.2 (GND), C2025.2 (GND), C2026.2 (GND), C2027.2 (GND), C2032.2 (GND), C2042.2 (GND), C2052.2 (GND), C2062.2 (GND), C20120.2 (GND), C20121.2 (GND), C20122.2 (GND), C20123.2 (GND), C20130.2 (GND), C20131.2 (GND), C20132.2 (GND), C20220.2 (GND), C20221.2 (GND), C20222.2 (GND), C20223.2 (GND), C20230.2 (GND), C20231.2 (GND), C20232.2 (GND), R2.2 (GND), R4.2 (GND), R9.2 (GND), R10.2 (GND), R12.2 (GND), R20.2 (GND), R25.2 (GND), R2012.2 (GND), R2032.2 (GND), R2042.2 (GND), R2052.2 (GND), R2062.2 (GND), U1.4 (GND), U13.1 (GND), U13.2 (GND), U13.3 (GND), U13.4 (GND), U13.7 (GND); also elsewhere on the board
I2Ct_SCL: R6.2 (I2Ct_SCL), U13.6 (I2Ct_SCL); also elsewhere on the board
I2Ct_SDA: R5.2 (I2Ct_SDA), U13.5 (I2Ct_SDA); also elsewhere on the board
ILIM_HIZ: R4.1 (ILIM_HIZ); also elsewhere on the board
LDO_1V5: C2.1 (LDO_1V5); also elsewhere on the board
LDO_3V3: C1.1 (LDO_3V3), R5.1 (LDO_3V3), R6.1 (LDO_3V3), R7.1 (LDO_3V3), U13.8 (LDO_3V3); also elsewhere on the board
L_1V2_MIPI0: C2016.1 (L_1V2_MIPI0), C20123.1 (L_1V2_MIPI0), FB2016.2 (L_1V2_MIPI0); also elsewhere on the board
L_1V2_MIPI1: C2017.1 (L_1V2_MIPI1), FB2017.2 (L_1V2_MIPI1); also elsewhere on the board
L_1V8_IO: C2013.1 (L_1V8_IO), C20121.1 (L_1V8_IO), FB2013.2 (L_1V8_IO); also elsewhere on the board
L_1V15_CORE: C2015.1 (L_1V15_CORE), C20122.1 (L_1V15_CORE), FB2015.2 (L_1V15_CORE); also elsewhere on the board
L_1V15_HDMI: C2014.1 (L_1V15_HDMI), FB2014.2 (L_1V15_HDMI); also elsewhere on the board
L_3V3_HDMI: C2011.1 (L_3V3_HDMI), C20120.1 (L_3V3_HDMI), FB2011.2 (L_3V3_HDMI), R2010.2 (L_3V3_HDMI), R2011.2 (L_3V3_HDMI); also elsewhere on the board
L_3V3_IO: C2012.1 (L_3V3_IO), FB2012.2 (L_3V3_IO); also elsewhere on the board
L_BIASDA: C20130.1 (L_BIASDA); also elsewhere on the board
L_BRIDGE_INT: R2012.1 (L_BRIDGE_INT); also elsewhere on the board
L_HPDI: R2011.1 (L_HPDI); also elsewhere on the board
L_PCKIN: C20131.1 (L_PCKIN); also elsewhere on the board
L_PFIL: C20132.1 (L_PFIL); also elsewhere on the board
L_REXT: R2010.1 (L_REXT); also elsewhere on the board
MODE_5V: R25.1 (MODE_5V); also elsewhere on the board
PD_IRQ_N: R7.2 (PD_IRQ_N); also elsewhere on the board
PMID: C13.1 (PMID), C14.1 (PMID), C15.1 (PMID); also elsewhere on the board
PROG: R12.1 (PROG); also elsewhere on the board
REG_1V2_FB: R2051.2 (REG_1V2_FB), R2052.1 (REG_1V2_FB); also elsewhere on the board
REG_1V8_FB: R2041.2 (REG_1V8_FB), R2042.1 (REG_1V8_FB); also elsewhere on the board
REG_1V15_FB: R2061.2 (REG_1V15_FB), R2062.1 (REG_1V15_FB); also elsewhere on the board
REG_3V3_FB: R2031.2 (REG_3V3_FB), R2032.1 (REG_3V3_FB); also elsewhere on the board
R_1V2_MIPI0: C2026.1 (R_1V2_MIPI0), C20223.1 (R_1V2_MIPI0), FB2026.2 (R_1V2_MIPI0); also elsewhere on the board
R_1V2_MIPI1: C2027.1 (R_1V2_MIPI1), FB2027.2 (R_1V2_MIPI1); also elsewhere on the board
R_1V8_IO: C2023.1 (R_1V8_IO), C20221.1 (R_1V8_IO), FB2023.2 (R_1V8_IO); also elsewhere on the board
R_1V15_CORE: C2025.1 (R_1V15_CORE), C20222.1 (R_1V15_CORE), FB2025.2 (R_1V15_CORE); also elsewhere on the board
R_1V15_HDMI: C2024.1 (R_1V15_HDMI), FB2024.2 (R_1V15_HDMI); also elsewhere on the board
R_3V3_HDMI: C2021.1 (R_3V3_HDMI), C20220.1 (R_3V3_HDMI), FB2021.2 (R_3V3_HDMI), R2020.2 (R_3V3_HDMI), R2021.2 (R_3V3_HDMI); also elsewhere on the board
R_3V3_IO: C2022.1 (R_3V3_IO), FB2022.2 (R_3V3_IO); also elsewhere on the board
R_BIASDA: C20230.1 (R_BIASDA); also elsewhere on the board
R_BRIDGE_INT: R2022.1 (R_BRIDGE_INT); also elsewhere on the board
R_HPDI: R2021.1 (R_HPDI); also elsewhere on the board
R_PCKIN: C20231.1 (R_PCKIN); also elsewhere on the board
R_PFIL: C20232.1 (R_PFIL); also elsewhere on the board
R_REXT: R2020.1 (R_REXT); also elsewhere on the board
SW1: C17.2 (SW1), L3.1 (SW1); also elsewhere on the board
SW2: C18.2 (SW2), L3.2 (SW2); also elsewhere on the board
TS: R9.1 (TS), R10.1 (TS); also elsewhere on the board
USB1V05_FB: C67.2 (USB1V05_FB), R19.2 (USB1V05_FB), R20.1 (USB1V05_FB), U1.3 (USB1V05_FB)
USB1V05_PG: R21.2 (USB1V05_PG), U1.2 (USB1V05_PG)
USB1V05_SW: L1.1 (USB1V05_SW), U1.5 (USB1V05_SW)
WIFI_ENABLE_N: R22.2 (WIFI_ENABLE_N); also elsewhere on the board

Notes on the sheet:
BOARD2 SUPPORT
Recovered from approved PCB placement; passive pin types marked VERIFY until vendor-symbol audit
